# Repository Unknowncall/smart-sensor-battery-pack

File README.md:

# Smart Sensor Battery Pack
This is the experimental battery charging PCB designed for my YouTube video. You can see the full build process, design theory, and assembly in the video below:

> **In this fork:** [`hardware/soil-sensor/`](hardware/soil-sensor/) is a new,
> separate design: an all-in-one ESP32-C6 soil sensor with an on-board 18650,
> USB-C charging and a capacitive probe, fully JLC-assembled. [`jlcpcb/`](jlcpcb/)
> and [`enclosure/`](enclosure/) hold order files and a printed case for the
> original board below.

### Please note: 
This board is currently missing a pull up resistor on the SCL/SDA lines - I will be adding this very soon. Software correction is possible using the XIAO pull-ups, and closing the FET early in the boot cycle. So using the board in its current form just makes the code a little more verbose. 

```
# Force GPIO18 LOW (Turns P-Channel MOSFET on)
# Set priority such that this runs before i2c initialises
esphome:
  on_boot:
    - priority: 1200
      then:
        - lambda: |-
            gpio_config_t io_conf = {};
            io_conf.pin_bit_mask = (1ULL<<18);
            io_conf.mode = GPIO_MODE_OUTPUT;
            io_conf.pull_up_en = GPIO_PULLUP_DISABLE;
            io_conf.pull_down_en = GPIO_PULLDOWN_DISABLE;
            io_conf.intr_type = GPIO_INTR_DISABLE;
            gpio_config(&io_conf);
            gpio_set_level(GPIO_NUM_18, 0);

# Software accessible pullups
i2c:
  sda_pullup_enabled: true
  scl_pullup_enabled: true

```

## ⚠️ Safety Warning
This board involves **Lithium-Ion battery charging**. 
*   This is an **experimental prototype** from a hobbyist. **I am not a professional engineer**. It has **not** been certified by safety agencies (UL, CE, etc.).
*   Lithium batteries can be dangerous if mishandled (risk of thermal runaway, fire, explosion, and serious injury).
*   **DO NOT leave this device unattended with a battery connected**
*   By using these files, you agree that you are solely responsible for verifying the safety of the circuit.

## License & Liability

### 1. Non-Commercial Use Only
This project is shared under the [Creative Commons Attribution-NonCommercial-ShareAlike 4.0 International](https://creativecommons.org/licenses/by-nc-sa/4.0/) license.
*  **You are free to:** Download, modify, and build this for personal use or learning.
*  **You may NOT:** Sell this board, use it in a product you sell, or use these files for any commercial purpose.
*  If you modify and share this design, you must share it under this same license.

### 2. No Liability (Disclaimer)
These files are provided "As Is" for educational purposes ONLY. I am sharing my personal project notes. **I accept no liability for any damage, injury, or loss** that occurs from the use or assembly of these files. Use them at your own risk.

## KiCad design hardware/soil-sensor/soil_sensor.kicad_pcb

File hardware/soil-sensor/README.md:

# Soil sensor v1

One board that is the whole sensor: ESP32-C6 (WiFi, ESPHome), an 18650 cell in
an on-board holder with USB-C charging and protection, a capacitive soil probe
made of copper under solder mask, and an SHTC3 for air temperature/humidity.
Fully assembled by JLCPCB; nothing to solder. Drop in a cell, plug in USB-C,
flash.

| | |
|---|---|
| Size | 25 x 222 mm, 2 layers, 1.6 mm, black, LeadFree HASL |
| Push into soil up to | the **SOIL LINE** silkscreen (70 mm of probe below it) |
| Battery | one 18650 (unprotected is fine: XB5353A protects it), + at the USB end |
| Charging | USB-C, ~500 mA (TP4056), red LED while charging |
| Readings | soil moisture %, air temperature, air humidity, battery V and % |
| Battery life | estimate 3-4 months per charge at one reading / 10 min (not measured) |

Design: [`docs/superpowers/specs/2026-11-16-soil-probe-board-design.md`](../../docs/superpowers/specs/2026-11-16-soil-probe-board-design.md).
Wiring for review: [`NETLIST.md`](NETLIST.md).

## Ordering at JLCPCB

Upload from [`jlcpcb/`](jlcpcb/):

1. `soil_sensor-gerbers.zip` as the Gerber file. Choose **black**, **LeadFree HASL**
   (OSP blocks Economic assembly), 1.6 mm.
2. PCB Assembly: **Economic**, **Top side**, quantity 2 (or 5).
3. `BOM-JLCPCB.csv` and `CPL-JLCPCB.csv`. Turn on **Confirm Parts Placement**
   so a JLC engineer checks rotations; the board was laid out by script and
   nobody has eyeballed every part's pin-1 marking in JLC's viewer yet.
4. Pick a Product Description (e.g. Research/Education/DIY -> DIY Hobby
   Circuit Board) or "Save to cart" silently does nothing.

Six parts carry JLC's $3.09 Extended fee (ESP32-C6-WROOM-1, XC6220, USB-C,
SHTC3, 18650 holder, XB5353A); everything else is Basic or Preferred.

## Firmware

```bash
cd firmware
cp secrets.example.yaml secrets.yaml   # fill in WiFi and keys
uvx esphome run soil-sensor.yaml
```

Calibrate once: read **Soil probe voltage** in Home Assistant with the probe in
dry air and in a glass of water, and put those two numbers into
`soil_dry_v` / `soil_wet_v` at the top of the YAML.

## Rebuilding the board files

Everything is generated; don't hand-edit the `.kicad_pcb`.

```bash
tools/fetch_parts.sh                    # footprints + Freerouting (needs Java 25+)
tools/route.sh                          # build, auto-route, stitch GND, DRC
tools/kpy gen/export_jlc.py             # gerbers, BOM, CPL into jlcpcb/
tools/kpy -m pytest tests -q            # 75 checks (netlist, placement, DRC, outputs)
```

Routing isn't reproducible run to run; the committed board is the one that was
checked.

## Not verified yet

Everything above is verified in software only (netlist checks, KiCad DRC,
ESPHome compile). Power-up, flashing, probe readings, charging and battery life
can only be checked once boards arrive.

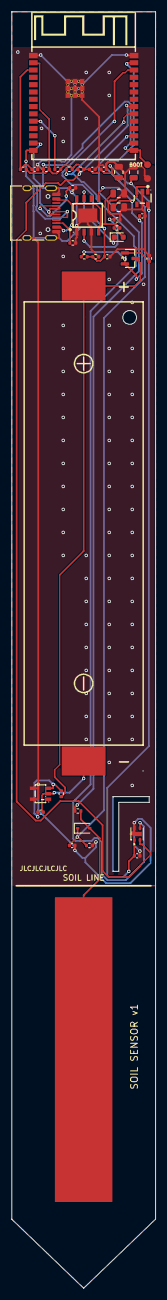
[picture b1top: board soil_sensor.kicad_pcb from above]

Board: 2 copper layers, 25.0 x 222.0 mm, 40 parts (0 on the bottom side), 24 nets.

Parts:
BT1: BH-18650-B1BA002
C_BATADC: 100nF; C_0402_1005Metric
C_BULK: 22uF; C_0805_2012Metric
C_EN: 1uF; C_0402_1005Metric
C_LDOIN: 1uF; C_0402_1005Metric
C_LDOOUT: 1uF; C_0402_1005Metric
C_MCU1: 10uF; C_0805_2012Metric
C_MCU2: 100nF; C_0402_1005Metric
C_PROT: 100nF; C_0402_1005Metric
C_RH: 100nF; C_0402_1005Metric
C_SOIL: 100nF; C_0402_1005Metric
C_VBAT: 10uF; C_0805_2012Metric
C_VBUS: 10uF; C_0805_2012Metric
D_PROBE: 1N4148WS; D_SOD-323
E_PROBE: electrode; PROBE_ELECTRODE
J_USB: TYPE-C-31-M-12; USB_C_Receptacle_HRO_TYPE-C-31-M-12
LED_CHG: Red; LED_0603_1608Metric
Q_REV: AO3401A; SOT-23
R_BAT1, R_BAT2: 1M; R_0402_1005Metric
R_BOOT: 10k; R_0402_1005Metric
R_CC1, R_CC2: 5.1k; R_0402_1005Metric
R_DRV: 1k; R_0402_1005Metric
R_EN: 10k; R_0402_1005Metric
R_IO8: 10k; R_0402_1005Metric
R_LED: 1k; R_0402_1005Metric
R_PROG: 2.4k; R_0402_1005Metric
R_PROT: 100R; R_0402_1005Metric
R_QG: 100k; R_0402_1005Metric
R_SCL: 10k; R_0402_1005Metric
R_SDA: 10k; R_0402_1005Metric
R_SOIL: 1M; R_0402_1005Metric
TP_BOOT: TP_BOOT; TESTPAD_1.2
TP_GND: TP_GND; TESTPAD_1.2
U_CHG: TP4056; TP4056_ESOP-8
U_LDO: XC6220B331MR; XC6220_SOT-23-5
U_MCU: ESP32-C6-WROOM-1-N8; ESP32-C6-WROOM-1
U_PROT: XB5353A; XB5353A_SOT-23-5
U_RH: SHTC3; SHTC3_DFN-4

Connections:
3V3: C_BULK.1, C_LDOOUT.1, C_MCU1.1, C_MCU2.1, C_RH.1, R_BOOT.2, R_EN.2, R_IO8.2, R_SCL.2, R_SDA.2, U_LDO.5, U_MCU.2, U_RH.1
BAT_ADC: C_BATADC.1, R_BAT1.2, R_BAT2.1, U_MCU.26
BOOT: R_BOOT.1, TP_BOOT.1, U_MCU.15
CC1: J_USB.A5, R_CC1.1
CC2: J_USB.B5, R_CC2.1
CHRG_N: LED_CHG.1, U_CHG.7
EN: C_EN.1, R_EN.1, U_MCU.3
GND: C_BATADC.2, C_BULK.2, C_EN.2, C_LDOIN.2, C_LDOOUT.2, C_MCU1.2, C_MCU2.2, C_RH.2, C_SOIL.2, C_VBAT.2, C_VBUS.2, J_USB.A1, J_USB.A12, J_USB.B1, J_USB.B12, J_USB.SH, R_BAT2.2, R_CC1.2, R_CC2.2, R_PROG.2, R_QG.2, R_SOIL.2, TP_GND.1, U_CHG.1, U_CHG.3, U_CHG.9, U_LDO.2, U_MCU.1, U_MCU.28, U_MCU.29, U_MCU.30, U_MCU.31, U_MCU.32, U_MCU.33, U_MCU.34, U_MCU.35, U_MCU.36, U_MCU.37, U_PROT.4, U_PROT.5, U_RH.4, U_RH.5
IO8: R_IO8.1, U_MCU.10
LED_A: LED_CHG.2, R_LED.1
PROBE_DRV: R_DRV.1, U_MCU.17
PROBE_EL: D_PROBE.2, E_PROBE.1, R_DRV.2
PROG: R_PROG.1, U_CHG.2
PROT_VDD: C_PROT.1, R_PROT.2, U_PROT.3
QG: Q_REV.1, R_QG.1
SCL: R_SCL.1, U_MCU.21, U_RH.2
SDA: R_SDA.1, U_MCU.20, U_RH.3
SOIL_ADC: C_SOIL.1, D_PROBE.1, R_SOIL.1, U_MCU.27
USB_DN: J_USB.A7, J_USB.B7, U_MCU.13
USB_DP: J_USB.A6, J_USB.B6, U_MCU.14
VBAT: C_LDOIN.1, C_VBAT.1, Q_REV.2, R_BAT1.1, U_CHG.5, U_LDO.1, U_LDO.3
VBUS: C_VBUS.1, J_USB.A4, J_USB.A9, J_USB.B4, J_USB.B9, R_LED.2, U_CHG.4, U_CHG.8
VCELL_N: BT1.1, C_PROT.2, U_PROT.2
VCELL_P: BT1.2, Q_REV.3, R_PROT.1
